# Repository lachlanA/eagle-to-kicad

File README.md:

### **Converting from Eagle to KiCad.**
*    [Quick Introduction Video (DEAD LINK, MOVING to NEW SERVER)](http://cosmosc.com/video/testtital.mp4)  
     *Recommended video player [Firefox 87.0+](https://www.mozilla.org/en-US/firefox/desktop/) with [VLC video player plugin](http://www.videolan.org/vlc/)*  

* The following 5 **ulp** (eagle *user script file*) and one **ulp** include file, work together or stand alone to convert **Eagle** *sch/pcb* version 6.xx*(7.xx-8.xx maybe?)* file(s) and any version of Eagle lib(*lbr*) to **KiCad** *sch/pcb* and *lib/mod* files.  

* The Programs will do
    * Eagle multi sheet schematic to KiCad multi sheets.  
	* Global and local net labels for multi sheets. *(This is a real nasty bit of hacking!)*
	* Multi part gates.  
	* Build KiCad PCB modules and sch libs from Eagle sch.  
	* Make project director to store all the converted files.  
	* And basic error checking.  
	* Eagle 6.xx(7.xx-8.xx?) PCB files can be directly import to KiCad.  
	* Eagle *LBR*s (any version of Eagle libs or size ) can be converted to KiCad lib/mod using eagle-lbr2kicad-1.0.ulp see [Eagle Lib conversion]( https://github.com/lachlanA/eagle-to-kicad-libs) for more details.  
	* Converts VIA to Pads, which helps with KiCad's flood fill, when VIAs have no connections.  
	* Documents fills over SMD pads on Eagle Layer 155,156  
	* Documents on layer's 150,152,153,154 of (Eagle) the unconnected VIAs and tracks.  
	* The **[examples](https://github.com/lachlanA/eagle-to-kicad/tree/master/examples)** directory contains a number of converted schematics/boards.  

* By using the following **ulp**s  a consistent link from the schematic to PCB is maintained so forward and backward net-list annotations work under KiCad!  

* **WARNINGS, AND NASTY SURPRISES, PLEASE READ!!!**
* **Only works correctly for version 4.7, or 5.1.(X?) of KiCad, it may not on other version.**
* **In KiCad Eagle PCB import of vias and tracks don't retain their NET information if they are not connected to a pad with a track, whereas they do in Eagle, (KiCad assigns a null net-name on Eagle PCB import in KiCad's Pcbnew).***  
***The result will be KiCad flood fill will not connect to them!!! There is an option to convert and document on layers 150,152,153,154 of (Eagle) the unconnected VIAs and tracks which will make finding and fixing the problem much easier.***
* ***Schematics wire's/nets can terminate in a bus or onto another wire/net/pad and not be connected in Eagle!!
Whereas in KiCad schematic wires to wires and wires to pads which terminates at the same location will be connected!!***  
* ***Eagle oval pad shapes are not supported in KiCad, you will only end up with a round pad!!***  
* ***Eagle PCB design rules are not imported by KiCads Pcbnew.***  

### Installing.
* Download the zip file, and unzip using your favorite zip program to your target directory *OR* if your prefer git:

			git clone https://github.com/lachlanA/eagle-to-kicad.git  

* **WARNING:**  The ULPs file-name will conflict with Eagles ULPs file-names so  
  **DO NOT install them in Eagle's ULP directory**  

* There are 5 **ULPs** and one **ULP** include file have been hack together.  
***run-me-first-from-eagle-sch.ulp*** .....   stage 1: Start here,  script missing number(s) to parts prefixes.  
***fix_via_hack.ulp*** ..............................   stage 2: Converts unconnected VIAs to pads.  
***eagle6xx-sch-to-kicad-sch.ulp*** ....    stage 3: Build sch and project files, etc  
***exp-lbrs.ulp*** .......................................   stage 4: Extract libs from eagle schematic/PCB  
***eagle-lbr2kicad-1.0.ulp***....................  stage 5: Converts Eagle lbr to KiCad lib/mod  
***eagle_to_kicad_include.inc*** ..........  Include file used by the other 4 ULP\s  

### HOW TO RUN THE ULPs 
 
 **WARNING Always backup your Eagle sch/PCB files before running this program!**  
 
1. Start your Eagle program *(Make sure your using  version 6.xx of Eagle)*

2. Open the eagle sch/PCB  file you wish to convert. Make sure the eagle sch and PCB files are both, Correct and pass all ERC/DRC checks in Eagle.  

3. Next Open the top left hand  **File menu** and select  **Run ULP**  

4. A file requester window will open. Use this to find the location of the ***run-me-first-from-eagle-sch.ulp*** ULP you download from this website. We use this script to make sure all part prefixes are ending in a number  IE:   R0,  X1   etc. as KiCad will ask to renumber any prefix which does not end in a number. *(It may do this any way, but don't worry it won't change any prefixes which have already been numbered unless you tell it too!)*  Keeping prefixes consistent from schematic to PCB will allow net-list forward and back annotation to work in KiCad. Select **OK** *(this will run the script)*.  When this completes all references without a number should have a number appended to them. Note: This number will start from the largest reference number on the sch/PCB.

5. Next stage will run automatically, ***fix_via_hack.ulp*** This will check for free unconnected VIAs and convert them to pads,  this is very much a hack, as it changes the Eagle sch/PCB files.  The changed files are saved in ***targetdir/modified_eagle_files/*** There are 2 option's Document the VIAs/pads buy putting a ***>*** and net lable name on the VIA/pad on **layer 51** for Eagle, and **Dwgs.User** for KiCad. Second option is to Not to convert the VIAs to pads.  
The ulp hack adds pad's to the sch file, at **X,Y 0,0** this may conflict with any net/part at this location, so please move the sch/PCB contents so there are no parts/nets at this location before running the script.
You may getting warnings from Eagle about connecting net??? to a power plan net, just click OK, as this is normal for this script.

6. Next stage will run automatically. Set the option/location of the download ULP. And also Make sure you make/select a ***clean target directory*** where all the KiCad files will be put. Select OK, And with luck you should have sch part done. The previous ULP will link automatically to ***exp-lbrs.ulp*** for the  next step: If you have selected extract the KiCad lib's from Eagle sch/PCB *(The default).* This ULP will build Eagle lbr file, *Note: this can be a very slow process,  and will leave the Eagle PCB editor window open when complete*. Just ignore this for the moment. If this complete OK, the previous ULP will link to ***eagle-lbr2kicad-1.0.ulp*** which will convert the Eagle lbr file to a KiCad lib/mod files.  The ***eagle-lbr2kicad-1.0.ulp*** window will open with quite a few options. Just select OK for the moment.  And if *Murphy's Law is sound asleep* we should have the target directory with all the converted files, including KiCad project files. But with one exception, it will be missing KiCad PCB file.

7. For this, we need to Open KiCad's **pcbnew** program directly, at the command prompt ("c:\Program Files\KiCad\bin\pcbnew.exe"). *If you make the mistake of not opening **pcbnew** directly, and instead chose to run it from KiCad's **pcbnew**  menu. You will have no option for importing the Eagle 6 PCB file!*  In Pcbnew click on **File->Import Non-KiCad Board File...**, a window will pop-up. Select the PCB eagle file linked to the eagle sch file we used at the beginning. On the lower right side you will have a drop down menu box option, select **Eagle ver. 6.x XML PCB files (\*.b**, and press OK. After importing the Eagle PCB file, (without errors I hope). Do a **SAVE AS** to **PROJECTNAME.kicad_pcb** to the new target directory *(where you saved the output from to preceding ULP's to).* **PROJECTNAME** being the name you give to your project early on. As a helper a dummy kicad_pcb file with the correct name has been created in the target directory which you can use to do a Save-As to.

8. Next step is to check the KiCad **sch** and KiCad **PCB** are consistent for parts and nets. Start **KiCad**, and open the project in the newly created target directory. Open the sch file. And if it was converted from the single sch file, you should have the **sch** file in the display. Or multi sheet **sch** file you will have a number of small boxes spread across the page. Each one of those boxes being a converted Eagle sub-sheet. Click on the first one and check for errors. All being good, click on Generate Net-list, and click OK. It may ask to Annotate the **schematic**. If so do the Annotation step. And then come back and click on Generate net-list. And Generate it.

9. Next click on **CvPcb**, this assigns the PCB footprints with the sch parts. Most likely you will get the following warning: *Some of the assigned footprints are legacy entries (are missing lib nicknames). Would you like CvPcb to attempt to convert them to the new required FPID format? (If you answer no, then these assignments will be cleared out and you will have to re-assign these footprints yourself.)* Just click the yes button. And a window will open up listing all the parts and footprints which it has assigned. Under FILE menu click Save. And then File Close.

10. Next Clink on **PcbNew** button on the top menu, and the PCB should open up. Now click on the **NetList** and a window should open up, from there click on Read Current Net-list. All going well you should not have any extra parts added, and only a few warning's about changing net list names.  And you should be done. Please check over the converted **sch/PCB** as there are many things which can go wrong! While I have tried to catch as many conversion problem, I expect there many still waiting to be found. ***So check and triple check the results!!!***

**NOTES:**   For more info on KiCad https://www.kicad.org/display/KICAD/Installing+KiCad  
As KiCad is the process of major upgrade, and enhancement. Please be nice when asking questions of the Development team. I think you will love the new Push and shove router. This feature alone makes it worth while moving from Eagle to KiCad. I hope these ULPs make the job a lot easier.

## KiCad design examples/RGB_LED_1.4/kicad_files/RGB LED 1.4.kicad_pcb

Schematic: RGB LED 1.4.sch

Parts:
C1, C2, C3: 0.1uF; CAP-PTH-SMALL
IC1, IC2, IC3: TLC9450NT; DIL28-3
JP2: ARDUINO POWER; 1X06_LOCK
JP3: ARDUINO ANALOG; 1X06_LOCK
JP4: ARDUINO D13-8; 1X08_LOCK
JP5: ARDUINO D7-0; 1X08_LOCK
JP11: 1X02_LOCK
JP12, JP13: 1X05_LOCK
JP20, JP21: 1X04_LOCK
LED11, LED12, LED13, LED14, LED21, LED22, LED23, LED24, LED31, LED32, LED33, LED34, LED41, LED42, LED43, LED44: LED-TRICOLOR-THROUGHHOLE
R1, R2, R3: 2K; 0309_12
R4: 10K; 0309_12
SW1, SW2, SW3: TACTILE-PTH
SWRESET45: RESET; TACTILE-PTH

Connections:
B11: IC3.28 (OUT0), LED11.GRN
B12: IC3.1 (OUT1), LED12.GRN
B13: IC3.2 (OUT2), LED13.GRN
B14: IC3.3 (OUT3), LED14.GRN
B21: IC3.4 (OUT4), LED21.GRN
B22: IC3.5 (OUT5), LED22.GRN
B23: IC3.6 (OUT6), LED23.GRN
B24: IC3.7 (OUT7), LED24.GRN
B31: IC3.8 (OUT8), LED31.GRN
B32: IC3.9 (OUT9), LED32.GRN
B33: IC3.10 (OUT10), LED33.GRN
B34: IC3.11 (OUT11), LED34.GRN
B41: IC3.12 (OUT12), LED41.GRN
B42: IC3.13 (OUT13), LED42.GRN
B43: IC3.14 (OUT14), LED43.GRN
B44: IC3.15 (OUT15), LED44.GRN
BLANK: IC1.23 (BLANK), IC2.23 (BLANK), IC3.23 (BLANK), JP4.3, JP21.3, R4.1
G11: IC2.28 (OUT0), LED11.BLU
G12: IC2.1 (OUT1), LED12.BLU
G13: IC2.2 (OUT2), LED13.BLU
G14: IC2.3 (OUT3), LED14.BLU
G21: IC2.4 (OUT4), LED21.BLU
G22: IC2.5 (OUT5), LED22.BLU
G23: IC2.6 (OUT6), LED23.BLU
G24: IC2.7 (OUT7), LED24.BLU
G31: IC2.8 (OUT8), LED31.BLU
G32: IC2.9 (OUT9), LED32.BLU
G33: IC2.10 (OUT10), LED33.BLU
G34: IC2.11 (OUT11), LED34.BLU
G41: IC2.12 (OUT12), LED41.BLU
G42: IC2.13 (OUT13), LED42.BLU
G43: IC2.14 (OUT14), LED43.BLU
G44: IC2.15 (OUT15), LED44.BLU
GND: C1.2, C2.2, C3.2, IC1.22 (GND), IC1.27 (VPRG), IC2.22 (GND), IC2.27 (VPRG), IC3.22 (GND), IC3.27 (VPRG), JP2.3, JP20.2, R1.1, R2.1, R3.1, SW1.3, SW1.4, SW2.3, SW2.4, SW3.3, SW3.4, SWRESET45.3, SWRESET45.4
GSCLK: IC1.18 (GSCLK), IC2.18 (GSCLK), IC3.18 (GSCLK), JP5.4, JP21.4
unnamed: IC1.17 (SOUT), IC2.26 (SIN)
unnamed: IC2.17 (SOUT), IC3.26 (SIN)
unnamed: JP12.3, SW1.1, SW1.2
unnamed: IC3.20 (IREF), R3.2
unnamed: IC2.20 (IREF), R2.2
unnamed: IC1.20 (IREF), R1.2
unnamed: JP12.4, SW2.1, SW2.2
unnamed: JP12.5, SW3.1, SW3.2
R11: IC1.28 (OUT0), LED11.RED
R12: IC1.1 (OUT1), LED12.RED
R13: IC1.2 (OUT2), LED13.RED
R14: IC1.3 (OUT3), LED14.RED
R21: IC1.4 (OUT4), LED21.RED
R22: IC1.5 (OUT5), LED22.RED
R23: IC1.6 (OUT6), LED23.RED
R24: IC1.7 (OUT7), LED24.RED
R31: IC1.8 (OUT8), LED31.RED
R32: IC1.9 (OUT9), LED32.RED
R33: IC1.10 (OUT10), LED33.RED
R34: IC1.11 (OUT11), LED34.RED
R41: IC1.12 (OUT12), LED41.RED
R42: IC1.13 (OUT13), LED42.RED
R43: IC1.14 (OUT14), LED43.RED
R44: IC1.15 (OUT15), LED44.RED
RESET: JP2.6, SWRESET45.1, SWRESET45.2
SCLK: IC1.25 (SCLK), IC2.25 (SCLK), IC3.25 (SCLK), JP12.2, JP21.1
SCLK_DEF: JP4.6, JP13.2
SIN: IC1.26 (SIN), JP12.1
SIN_DEF: JP4.4, JP13.1
SOUT: IC3.17 (SOUT), JP20.3
SW1_DEF: JP5.3, JP13.3
SW2_DEF: JP5.5, JP13.4
SW3_DEF: JP5.8, JP13.5
VCC: C1.1, C2.1, C3.1, IC1.19 (DCPRG), IC1.21 (VCC), IC2.19 (DCPRG), IC2.21 (VCC), IC3.19 (DCPRG), IC3.21 (VCC), JP2.4, JP11.1, JP20.4, R4.2
VLED: JP11.2, JP20.1, LED11.GND (A), LED12.GND (A), LED13.GND (A), LED14.GND (A), LED21.GND (A), LED22.GND (A), LED23.GND (A), LED24.GND (A), LED31.GND (A), LED32.GND (A), LED33.GND (A), LED34.GND (A), LED41.GND (A), LED42.GND (A), LED43.GND (A), LED44.GND (A)
XLAT: IC1.24 (XLAT), IC2.24 (XLAT), IC3.24 (XLAT), JP4.2, JP21.2

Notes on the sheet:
HTINK RGB Shield 1.3
(C) 2009, Ben Combee
Creative Commons Attribution-Share Alike 3.0 License
http://combee.net/rgbshield
Allows connecting other voltage to LEDs

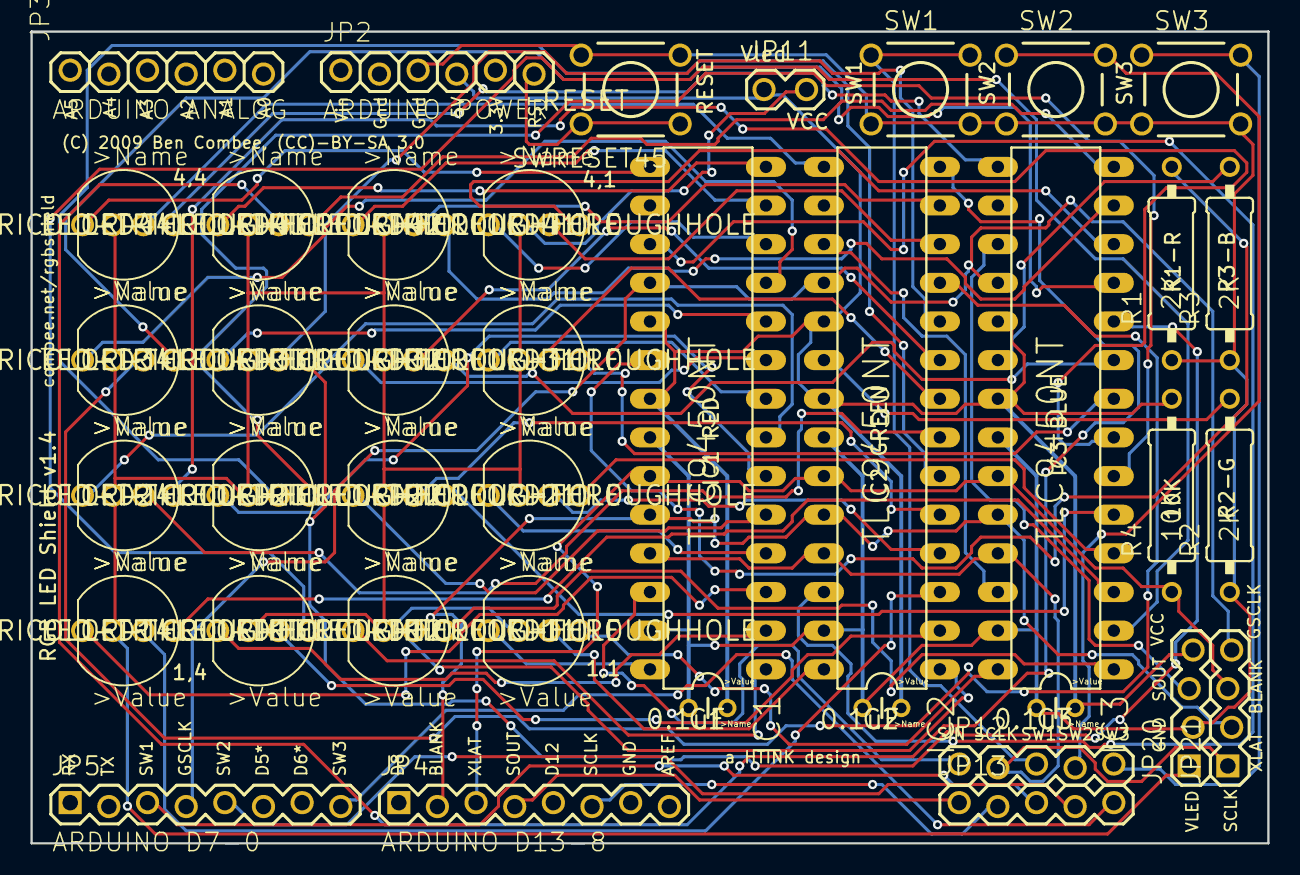
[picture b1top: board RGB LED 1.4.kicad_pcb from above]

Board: 2 copper layers, 81.3 x 53.3 mm, 39 parts (0 on the bottom side), 71 nets.

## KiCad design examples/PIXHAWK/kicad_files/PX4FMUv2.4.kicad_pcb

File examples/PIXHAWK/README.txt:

NOTE: ***** USE AT YOUR OWN RISK *****

This contains the eagle file's from PX4 Autopilot Project from git-hub, at https://github.com/PX4 which have been
convert to KiCad. Via's have been converted to Pad, and the modified Eagle files are in

  kicad_files/modified_eagle_files/

The original Eagle files are in

  eagle_original_files/

Also note the Eagle files have been converted to version 6.xx of eagle.
Note:  No Adjustment of power plan's had been made, you will need to adjust them to get correct connection's
       and spacing etc. And as away triple check you results.

sources at:   https://github.com/PX4

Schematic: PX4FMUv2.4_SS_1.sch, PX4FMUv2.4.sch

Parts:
C101: 0u1; PIXHAWK2_0402-CAP
C102, C103: 8p; PIXHAWK2_0402-CAP
R101: 470R; PIXHAWK2_0402-RES
R102: 10K; PIXHAWK2_0402-RES
U101: STM32F4X7VX; PIXHAWK2_TQFP100
U102: FM25V01; PIXHAWK2_SO08
X101: 3.2x2.5 mm / 24 MHz / 15 ppm; PIXHAWK2_OSCILLATOR-3.2X2.5

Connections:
!ACCEL_MAG_CS: U101.9 (PC15); also elsewhere on the board
!BARO_CS: U101.88 (PD7); also elsewhere on the board
!FMU-LED_AMBER: U101.43 (PE12); also elsewhere on the board
!FRAM_CS: U101.57 (PD10), U102.1 (!S)
!GYRO_CS: U101.7 (PC13); also elsewhere on the board
!MPU_CS: U101.17 (PC2); also elsewhere on the board
!SPI_EXT_NSS: U101.3 (PE4); also elsewhere on the board
!VBUS_VALID: U101.15 (PC0); also elsewhere on the board
!VDD_5V_HIPOWER_OC: U101.41 (PE10); also elsewhere on the board
!VDD_5V_PERIPH_EN: U101.67 (PA8); also elsewhere on the board
!VDD_5V_PERIPH_OC: U101.46 (PE15); also elsewhere on the board
!VDD_BRICK_VALID: U101.91 (PB5); also elsewhere on the board
!VDD_SERVO_VALID: U101.93 (PB7); also elsewhere on the board
ACCEL_DRDY: U101.90 (PB4); also elsewhere on the board
ALARM: U101.77 (PA15); also elsewhere on the board
BATT_CURRENT_SENS: U101.26 (PA3); also elsewhere on the board
BATT_VOLTAGE_SENS: U101.25 (PA2); also elsewhere on the board
CAN1_RX: U101.81 (PD0); also elsewhere on the board
CAN1_TX: U101.82 (PD1); also elsewhere on the board
CAN2_RX: U101.51 (PB12); also elsewhere on the board
CAN2_TX: U101.92 (PB6); also elsewhere on the board
FMU-CH1: U101.45 (PE14); also elsewhere on the board
FMU-CH2: U101.44 (PE13); also elsewhere on the board
FMU-CH3: U101.42 (PE11); also elsewhere on the board
FMU-CH4: U101.40 (PE9); also elsewhere on the board
FMU-CH5: U101.60 (PD13); also elsewhere on the board
FMU-CH6: U101.61 (PD14); also elsewhere on the board
FMU-I2C1_SCL: U101.95 (PB8); also elsewhere on the board
FMU-I2C1_SDA: U101.96 (PB9); also elsewhere on the board
FMU-I2C2_SCL: U101.47 (PB10); also elsewhere on the board
FMU-I2C2_SDA: U101.48 (PB11); also elsewhere on the board
FMU-SWCLK: U101.76 (PA14); also elsewhere on the board
FMU-SWDIO: U101.72 (PA13); also elsewhere on the board
FMU-SWO: U101.89 (PB3); also elsewhere on the board
FMU-UART4_RX: U101.24 (PA1); also elsewhere on the board
FMU-UART4_TX: U101.23 (PA0); also elsewhere on the board
FMU-UART7_RX: U101.38 (PE7); also elsewhere on the board
FMU-UART7_TX: U101.39 (PE8); also elsewhere on the board
FMU-UART8_RX: U101.97 (PE0); also elsewhere on the board
FMU-UART8_TX: U101.98 (PE1); also elsewhere on the board
FMU-USART2_CTS: U101.84 (PD3); also elsewhere on the board
FMU-USART2_RTS: U101.85 (PD4); also elsewhere on the board
FMU-USART2_RX: U101.87 (PD6); also elsewhere on the board
FMU-USART2_TX: U101.86 (PD5); also elsewhere on the board
FMU-USART3_CTS: U101.58 (PD11); also elsewhere on the board
FMU-USART3_RTS: U101.59 (PD12); also elsewhere on the board
FMU-USART3_RX: U101.56 (PD9); also elsewhere on the board
FMU-USART3_TX: U101.55 (PD8); also elsewhere on the board
FMU-VDD_3V3: C101.P$1 (1), U102.3 (!W), U102.7 (!HOLD), U102.8 (VDD); also elsewhere on the board
FMU_AUX_ADC1: U101.18 (PC3); also elsewhere on the board
FMU_AUX_ADC2: U101.33 (PC4); also elsewhere on the board
FRAM_MISO: U101.53 (PB14), U102.2 (Q)
FRAM_MOSI: U101.54 (PB15), U102.5 (D)
FRAM_SCK: U101.52 (PB13), U102.6 (C)
GND: C101.P$2 (2), C102.P$2 (2), C103.P$1 (1), R102.P$2 (2), U102.4 (VSS), X101.2 (NC_2), X101.4 (NC_4); also elsewhere on the board
GPIO_EXT_1: U101.8 (PC14); also elsewhere on the board
GYRO_DRDY: U101.35 (PB0); also elsewhere on the board
IO-USART1_TX: R101.P$2 (2); also elsewhere on the board
MAG_DRDY: U101.36 (PB1); also elsewhere on the board
MPU_DRDY: U101.62 (PD15); also elsewhere on the board
unnamed: C103.P$2 (2), U101.13 (OSC_OUT), X101.1
unnamed: C102.P$1 (1), U101.12 (OSC_IN), X101.3
unnamed: R101.P$1 (1), U101.69 (PA10)
OTG_FS_DM: U101.70 (PA11); also elsewhere on the board
OTG_FS_DP: U101.71 (PA12); also elsewhere on the board
PB2-BOOT1: R102.P$1 (1), U101.37 (PB2)
PRESSURE_SENS: U101.34 (PC5); also elsewhere on the board
SDIO_CK: U101.80 (PC12); also elsewhere on the board
SDIO_CMD: U101.83 (PD2); also elsewhere on the board
SDIO_D0: U101.65 (PC8); also elsewhere on the board
SDIO_D1: U101.66 (PC9); also elsewhere on the board
SDIO_D2: U101.78 (PC10); also elsewhere on the board
SDIO_D3: U101.79 (PC11); also elsewhere on the board
SERIAL_FMU_TO_IO: U101.63 (PC6); also elsewhere on the board
SERIAL_IO_TO_FMU: U101.64 (PC7); also elsewhere on the board
SPI_EXT_MISO: U101.4 (PE5); also elsewhere on the board
SPI_EXT_MOSI: U101.5 (PE6); also elsewhere on the board
SPI_EXT_SCK: U101.1 (PE2); also elsewhere on the board
SPI_INT_MISO: U101.31 (PA6); also elsewhere on the board
SPI_INT_MOSI: U101.32 (PA7); also elsewhere on the board
SPI_INT_SCK: U101.30 (PA5); also elsewhere on the board
VBUS: U101.68 (PA9); also elsewhere on the board
VDD_3V3_SENSORS_EN: U101.2 (PE3); also elsewhere on the board
VDD_5V_SENS: U101.29 (PA4); also elsewhere on the board

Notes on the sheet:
FMU SoC Ports FRAM
Note: MAG/ACCEL/GYRO_DRDY pins chosen for both timer capture and separate EXTI operaton. EXTI0 - TIM3_CH3 - GYRO1 EXTI1 - <free> EXTI2 - <free> EXTI3 - <free> EXTI4 - TIM3_CH1 - ACCEL EXTI5-9 - TIM3_CH2 - MAG
Timer allocation: PE9: TIM1_CH1: FMU-CH4 PE11: TIM1_CH2: FMU-CH3 PE13: TIM1_CH3: FMU-CH2 PE14: TIM1_CH4: FMU-CH1 PA15: TIM2_CH1: ALARM PB0: TIM3_CH3: GYRO1_DRDY PB1: TIM3_CH4: GYRO2_DRDY PB4: TIM3_CH1: ACCEL_DRDY PB5: TIM3_CH2: MAG_DRDY PD13: TIM4_CH2: FMU-CH5 PD14: TIM4_CH3: FMU-CH6 PD15: TIM4_CH4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
IO debug console
Spare ADC
ALL SHEETS SAME REVISION

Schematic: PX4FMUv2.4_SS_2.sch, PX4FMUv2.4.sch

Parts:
C201, C202: 0u1; PIXHAWK2_0402-CAP
D201, D202, D203: PESD0402-140; PIXHAWK2_0402-TVS
J201, J202, J203, J204: DF13C-6P-1.25V; CON-HIROSE-DF13_DF13C-6P-1.25V
L201, L202, L203: KNH16C104DA5TS; PIXHAWK2_KYOCERA-KNH16-DA
R201, R202, R203, R204, R205, R206, R207, R208, R209, R210, R211, R212, R213, R214, R215, R216: 120R; PIXHAWK2_0402-RES
U201, U202: TXS0108QFN20; PIXHAWK2_QFN20-RGY

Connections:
CAN2_RX: R216.P$1 (1); also elsewhere on the board
CAN2_TX: R215.P$1 (1); also elsewhere on the board
FMU-UART4_RX: U202.8 (A7); also elsewhere on the board
FMU-UART4_TX: U202.9 (A8); also elsewhere on the board
FMU-UART7_RX: U202.4 (A3); also elsewhere on the board
FMU-UART7_TX: U202.5 (A4); also elsewhere on the board
FMU-UART8_RX: U202.6 (A5); also elsewhere on the board
FMU-UART8_TX: U202.7 (A6); also elsewhere on the board
FMU-USART2_CTS: U201.9 (A8); also elsewhere on the board
FMU-USART2_RTS: U201.8 (A7); also elsewhere on the board
FMU-USART2_RX: U201.6 (A5); also elsewhere on the board
FMU-USART2_TX: U201.7 (A6); also elsewhere on the board
FMU-USART3_CTS: U201.3 (A2); also elsewhere on the board
FMU-USART3_RTS: U201.1 (A1); also elsewhere on the board
FMU-USART3_RX: U201.4 (A3); also elsewhere on the board
FMU-USART3_TX: U201.5 (A4); also elsewhere on the board
FMU-VDD_3V3: C201.P$1 (1), C202.P$1 (1), U201.2 (VCCA), U201.10 (OE), U201.19 (VCCB), U202.2 (VCCA), U202.10 (OE), U202.19 (VCCB); also elsewhere on the board
GND: C201.P$2 (2), C202.P$2 (2), D201.A, D202.A, D203.A, J201.6, J202.6, J203.6, J204.6, L201.P$3, L201.P$4, L201.P$5, L202.P$3, L202.P$4, L202.P$5, L203.P$3, L203.P$4, L203.P$5, U201.11 (GND), U202.11 (GND); also elsewhere on the board
unnamed: D201.C, J201.1, L201.P$2
unnamed: J203.4, R215.P$2 (2)
unnamed: J203.5, R216.P$2 (2)
unnamed: R201.P$1 (1), U201.20 (B1)
unnamed: R208.P$1 (1), U201.18 (B2)
unnamed: R202.P$1 (1), U201.17 (B3)
unnamed: R209.P$1 (1), U201.16 (B4)
unnamed: R203.P$1 (1), U201.15 (B5)
unnamed: R210.P$1 (1), U201.14 (B6)
unnamed: R204.P$1 (1), U201.13 (B7)
unnamed: R211.P$1 (1), U201.12 (B8)
unnamed: R207.P$1 (1), U202.13 (B7)
unnamed: R214.P$1 (1), U202.12 (B8)
unnamed: R205.P$1 (1), U202.17 (B3)
unnamed: R212.P$1 (1), U202.16 (B4)
unnamed: R206.P$1 (1), U202.15 (B5)
unnamed: R213.P$1 (1), U202.14 (B6)
unnamed: D203.C, J203.1, J204.1, L203.P$2
unnamed: D202.C, J202.1, L202.P$2
SERIAL1_CTS: J201.4, R211.P$2 (2)
SERIAL1_RTS: J201.5, R204.P$2 (2)
SERIAL1_RX: J201.3, R203.P$2 (2); also elsewhere on the board
SERIAL1_TX: J201.2, R210.P$2 (2); also elsewhere on the board
SERIAL2_CTS: J202.4, R208.P$2 (2)
SERIAL2_RTS: J202.5, R201.P$2 (2)
SERIAL2_RX: J202.3, R202.P$2 (2); also elsewhere on the board
SERIAL2_TX: J202.2, R209.P$2 (2); also elsewhere on the board
SERIAL3_RX: J203.3, R207.P$2 (2); also elsewhere on the board
SERIAL3_TX: J203.2, R214.P$2 (2); also elsewhere on the board
SERIAL4_RX: J204.3, R206.P$2 (2); also elsewhere on the board
SERIAL4_TX: J204.2, R213.P$2 (2); also elsewhere on the board
SERIAL5_RX: J204.5, R205.P$2 (2); also elsewhere on the board
SERIAL5_TX: J204.4, R212.P$2 (2); also elsewhere on the board
VDD_5V_HIPOWER: L201.P$1; also elsewhere on the board
VDD_5V_PERIPH: L202.P$1, L203.P$1; also elsewhere on the board

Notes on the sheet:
FMU Serial ports
SERIAL2
SERIAL1
SERIAL3
SERIAL4
Default GPS port

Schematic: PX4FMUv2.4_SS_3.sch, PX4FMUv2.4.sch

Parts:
J301: 47346-0001; PIXHAWK2_MOLEX-47346-0001
J302: DF13C-4P-1.25V; CON-HIROSE-DF13_DF13C-4P-1.25V
JX301: ARM_MINI_JTAG-SMT; PIXHAWK2_FTSH-105-01-XXX-DV-K
R301, R302, R303, R304, R305: 100K; PIXHAWK2_0402-RES
R306, R307: 1K5; PIXHAWK2_0402-RES
U301: 2908-05WB-MG; BASEBOARD_MICROSD
U302: NUF2042XV6; PIXHAWK2_SOT563-6

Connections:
FMU-I2C2_SCL: R306.P$1 (1); also elsewhere on the board
FMU-I2C2_SDA: R307.P$1 (1); also elsewhere on the board
FMU-SWCLK: JX301.4; also elsewhere on the board
FMU-SWDIO: JX301.2; also elsewhere on the board
FMU-SWO: JX301.6; also elsewhere on the board
FMU-VDD_3V3: JX301.1, R301.P$2 (2), R302.P$2 (2), R303.P$2 (2), R304.P$2 (2), R305.P$2 (2), R306.P$2 (2), R307.P$2 (2), U301.4 (VCC); also elsewhere on the board
GND: J301.GND (5), J301.GND1, J301.GND2, J301.GND3, J301.GND4, J302.4, JX301.3, JX301.5, JX301.9, U301.6 (GND), U302.2 (GND); also elsewhere on the board
OTG_DM1: J301.D- (2), J302.3, U302.1 (D1I)
OTG_DP1: J301.D+ (3), J302.2, U302.3 (D2I)
OTG_FS_DM: U302.6 (D1O); also elsewhere on the board
OTG_FS_DP: U302.4 (D2O); also elsewhere on the board
SDIO_CK: U301.5 (CLK); also elsewhere on the board
SDIO_CMD: R303.P$1 (1), U301.3 (CMD); also elsewhere on the board
SDIO_D0: R304.P$1 (1), U301.7 (D0); also elsewhere on the board
SDIO_D1: R305.P$1 (1), U301.8 (D1); also elsewhere on the board
SDIO_D2: R301.P$1 (1), U301.1 (D2); also elsewhere on the board
SDIO_D3: R302.P$1 (1), U301.2 (D3); also elsewhere on the board
VBUS: J301.VBUS (1), J302.1, U302.5 (VBUS); also elsewhere on the board

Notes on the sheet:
USB microSD Expansion
microSD
To be used with panel- mount micro USB connectors: - Amphenol MUSBK15230

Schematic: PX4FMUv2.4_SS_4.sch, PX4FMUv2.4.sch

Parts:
C401, C402: 0u1; PIXHAWK2_0402-CAP
D401, D402, D403, D404: PESD0402-140; PIXHAWK2_0402-TVS
J401, J405: DF13C-4P-1.25V; CON-HIROSE-DF13_DF13C-4P-1.25V
J402: DF13C-3P-1.25V; CON-HIROSE-DF13_DF13C-3P-1.25V
J403: DF13C-7P-1.25V; CON-HIROSE-DF13_DF13C-7P-1.25V
J404: DF13C-5P-1.25V; CON-HIROSE-DF13_DF13C-5P-1.25V
L401, L402, L403, L404: KNH16C104DA5TS; PIXHAWK2_KYOCERA-KNH16-DA
R401, R402: 1K5; PIXHAWK2_0402-RES
R403, R406, R407, R408: 10K/0.1%; PIXHAWK2_0402-RES
R404, R405, R409: 120R; PIXHAWK2_0402-RES
U401: MAX3051; PIXHAWK2_SOT23-8

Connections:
!SPI_EXT_NSS: J403.5; also elsewhere on the board
CAN1_RX: U401.4 (DOUT); also elsewhere on the board
CAN1_TX: U401.1 (DIN); also elsewhere on the board
CAN_H: J405.2, R409.P$1 (1), U401.7 (CANH); also elsewhere on the board
CAN_L: J405.3, R409.P$2 (2), U401.6 (CANL); also elsewhere on the board
FMU-I2C1_SCL: R401.P$1 (1), R404.P$1 (1); also elsewhere on the board
FMU-I2C1_SDA: R402.P$1 (1), R405.P$1 (1); also elsewhere on the board
FMU-VDD_3V3: C402.P$1 (1), R401.P$2 (2), R402.P$2 (2), U401.3 (VCC); also elsewhere on the board
FMU_AUX_ADC1: R408.P$1 (1); also elsewhere on the board
FMU_AUX_ADC1_PROT: J404.4, R408.P$2 (2)
FMU_AUX_ADC2: R407.P$1 (1); also elsewhere on the board
FMU_AUX_ADC2_PROT: J404.2, R407.P$2 (2)
GND: C401.P$2 (2), C402.P$2 (2), D401.A, D402.A, D403.A, D404.A, J401.4, J402.3, J403.7, J404.3, J404.5, J405.4, L401.P$3, L401.P$4, L401.P$5, L402.P$3, L402.P$4, L402.P$5, L403.P$3, L403.P$4, L403.P$5, L404.P$3, L404.P$4, L404.P$5, R403.P$1 (1), U401.2 (GND), U401.5 (SHDN), U401.8 (RS); also elsewhere on the board
GPIO_EXT_1: J403.6; also elsewhere on the board
unnamed: J401.2, R404.P$2 (2)
unnamed: J401.3, R405.P$2 (2)
unnamed: D402.C, J403.1, L402.P$2
unnamed: D401.C, J401.1, J402.1, L401.P$2
unnamed: D404.C, J405.1, L403.P$2
unnamed: D403.C, J404.1, L404.P$2
PRESSURE_SENS: C401.P$1 (1), R403.P$2 (2), R406.P$1 (1); also elsewhere on the board
PRESSURE_SENS_IN: J402.2, R406.P$2 (2); also elsewhere on the board
SPI_EXT_MISO: J403.3; also elsewhere on the board
SPI_EXT_MOSI: J403.4; also elsewhere on the board
SPI_EXT_SCK: J403.2; also elsewhere on the board
VDD_5V_PERIPH: L401.P$1, L402.P$1, L403.P$1, L404.P$1; also elsewhere on the board

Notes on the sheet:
SPI
PRESSURE
I2C1
AUX ADC PORTS
SPI I2C Analog pressure CAN Aux ADC ports
Note: SPI port is UNBUFFERED; only suitable for short connections.
Divider to scale from 5V to 3.3V (ratio of 0.5 chosen)

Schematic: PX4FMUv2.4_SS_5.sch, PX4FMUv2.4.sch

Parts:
C501, C506, C509, C511: 10u/10V; PIXHAWK2_0805-CAP
C502, C503, C507, C508, C514: 0u1; PIXHAWK2_0402-CAP
C504, C505: 10n; PIXHAWK2_0402-CAP
C510: 0u47; PIXHAWK2_0402-CAP
C512, C513: 2u2; PIXHAWK2_0603-CAP
C515: 0u01; PIXHAWK2_0603-CAP
U501: L3GD20; PIXHAWK2_L3G4200DH-MAN
U502: L3GD20H; PIXHAWK2_LGA-16L
U504: LSM303D; PIXHAWK2_LGA-16L
U505: MPU-6000; PIXHAWK2_QFN-24
U506: MS5611-01BA; PIXHAWK2_MS5611-01BA
X503: 0512811094; PIXHAWK2_51281-1094

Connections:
!ACCEL_MAG_CS: U504.8 (CS), X503.6; also elsewhere on the board
!BARO_CS: U506.5 (CSB2); also elsewhere on the board
!GYRO_CS: U501.5 (CS), U502.5 (CS), X503.7; also elsewhere on the board
!MPU_CS: U505.8 (/CS); also elsewhere on the board
ACCEL_DRDY: U504.11 (INT1), X503.3; also elsewhere on the board
GND: C501.P$2 (2), C502.P$2 (2), C503.P$2 (2), C504.P$2 (2), C505.P$2 (2), C506.P$2 (2), C507.P$2 (2), C508.P$2 (2), C509.P$2 (2), C511.P$2 (2), C512.P$2 (2), C513.P$2 (2), C514.P$2 (2), C515.P$2 (2), U501.8 (RES_P8_GND), U501.9 (RES_P9_GND), U501.10 (RES_P10_GND), U501.11 (RES_P11_GND), U501.12 (RES_P12_GND), U501.13 (GND), U502.9 (GND), U502.10 (GND), U502.11 (GND), U502.12 (GND), U502.13 (GND), U504.5 (GND), U504.10 (RSRV), U504.12 (GND), U504.13 (GND), U504.16 (GND), U505.1 (CLKIN), U505.18 (GND), U506.2 (PS), U506.3 (GND), X503.2; also elsewhere on the board
GYRO_DRDY: U501.6 (DRDY/INT2), U502.6 (DRDY/INT2), X503.5; also elsewhere on the board
MAG_DRDY: U504.9 (INT2), X503.4; also elsewhere on the board
MPU_DRDY: U505.12 (INT); also elsewhere on the board
unnamed: C509.P$1 (1), U504.15 (C1)
unnamed: C510.P$1 (1), U504.2 (SETC)
unnamed: C510.P$2 (2), U504.3 (SETP)
unnamed: C505.P$1 (1), U502.14 (CAP)
unnamed: C504.P$1 (1), U501.14 (PLLFILT)
unnamed: C512.P$1 (1), U505.10 (REGOUT)
unnamed: C515.P$1 (1), U505.20 (CPOUT)
SPI_INT_MISO: U501.4 (SDO/SA0), U502.4 (SDO/SA0), U504.7 (SDO/SA0), U505.9 (AD0/SDO), U506.6 (SDO), X503.9; also elsewhere on the board
SPI_INT_MOSI: U501.3 (SDA/SDI/SDO), U502.3 (SDA/SDI/SDO), U504.6 (SDA/SDI/SDO), U505.24 (SDA/SDI), U506.7 (SDI/SDA), X503.8; also elsewhere on the board
SPI_INT_SCK: U501.2 (SCL/SPC), U502.2 (SCL/SPC), U504.4 (SCL/SPC), U505.23 (SCL/SCLK), U506.8 (SCLK), X503.10; also elsewhere on the board
VDD_3V3_SENSORS: C501.P$1 (1), C502.P$1 (1), C503.P$1 (1), C506.P$1 (1), C507.P$1 (1), C508.P$1 (1), C511.P$1 (1), C513.P$1 (1), C514.P$1 (1), U501.1 (VDD_IO), U501.15 (RES_P15_VDD), U501.16 (VDD), U502.1 (VDD_IO), U502.15 (VDD), U502.16 (VDD), U504.1 (VDD_IO), U504.14 (VDD), U505.13 (VDD), U506.1 (VDD), X503.1; also elsewhere on the board

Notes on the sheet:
Sensors
Switch to L3GD20H once available (Q3/2013) WARNING: DIFFERENT HW, SW COMPATIBLE
NOTE: place 10uF cap close to gyros
Stuff option 1: L3GD20 (legacy gyro)
Stuff option 2: L3GD20H (replacement gyro)
Stuff option 4: onboard accel/mag
Valid stuff option combos: 1 + 4 + 5 2 + 4 + 5 3 + 5 ONLY DO NOT stuff 1 + 2 at the same time DO NOT stuff 3 with any of 1, 2 or 4
Stuff option 5: MPU6000
Stuff option 3: offboard gyro/accel/mag
STUFF C503 WITH 220R RESISTOR

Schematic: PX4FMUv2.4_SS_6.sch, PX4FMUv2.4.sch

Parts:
B601: MS621FE; PIXHAWK2_MS621FE
C601: 10u/25V; PIXHAWK2_0805-CAP
C602: 10n; PIXHAWK2_0402-CAP
C603: 1u; PIXHAWK2_0603-CAP
C604, C605: 22u/25V; PIXHAWK2_0805-CAP
C606, C607, C608, C609, C610, C612, C615, C616, C617: 0u1; PIXHAWK2_0402-CAP
C611, C613: 2u2; PIXHAWK2_0603-CAP
C614, C618: 100u; PIXHAWK2_1206-CAP
D2: RB751V40T1G; PIXHAWK2_SOD323
L603: KNH16C104DA5TS; PIXHAWK2_KYOCERA-KNH16-DA
Q601: MMBT3906LT1SMD; TRANSISTOR-PNP_SOT23-BEC
R602, R604: 1M; PIXHAWK2_0402-RES
R603: 10k; PIXHAWK2_0402-RES
R608: 1K; PIXHAWK2_0402-RES
R609, R610: 10K/0.1%; PIXHAWK2_0402-RES
R611, R615: 10K; PIXHAWK2_0402-RES
R616: 25K5; PIXHAWK2_0402-RES
R617: 16K5; PIXHAWK2_0402-RES
R620: 1k8; PIXHAWK2_0402-RES
R621: 10R; PIXHAWK2_0603-RES
R635: DNP / 10k; PIXHAWK2_0402-RES
S601: RESET; PIXHAWK2_EVQP7J01K
U101: STM32F4X7VX; PIXHAWK2_TQFP100
U601, U602: BQ24315; PIXHAWK2_QFN8-DSG
U603: MIC5332; PIXHAWK2_MLF-8-EPAD

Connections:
!VDD_5V_HIPOWER_OC: R602.P$1 (1), U601.4 (!FAULT); also elsewhere on the board
!VDD_5V_PERIPH_EN: R615.P$1 (1), U601.5 (!CE), U602.5 (!CE); also elsewhere on the board
!VDD_5V_PERIPH_OC: R604.P$1 (1), U602.4 (!FAULT); also elsewhere on the board
FMU-!RESET: C609.P$2 (2), R635.P$1 (1), S601.A1 (1), U101.14 (NRST), U603.3 (POR2); also elsewhere on the board
FMU-BOOT0: R611.P$2 (2), U101.94 (BOOT0); also elsewhere on the board
FMU-VDD_3V3: C603.P$1 (1), C604.P$1 (1), C606.P$1 (1), C607.P$1 (1), C608.P$1 (1), C610.P$1 (1), C612.P$1 (1), C616.P$1 (1), D2.A, R602.P$2 (2), R604.P$2 (2), U101.11 (VDD), U101.19 (VDD), U101.21 (VREF+), U101.22 (VDDA), U101.28 (VDD), U101.50 (VDD), U101.75 (VDD), U101.100 (VDD), U603.7 (VOUT2); also elsewhere on the board
FMU-VDD_5V5: C601.P$1 (1), C615.P$1 (1), L603.P$2, R603.P$1 (1), U603.1 (VIN), U603.4 (EN2)
GND: B601.2 (NEG), C601.P$2 (2), C602.P$1 (1), C603.P$2 (2), C604.P$2 (2), C605.P$2 (2), C606.P$2 (2), C607.P$2 (2), C608.P$2 (2), C609.P$1 (1), C610.P$2 (2), C611.P$2 (2), C612.P$2 (2), C613.P$2 (2), C614.P$2 (2), C615.P$2 (2), C616.P$2 (2), C617.P$2 (2), C618.P$2 (2), L603.P$3, L603.P$4, L603.P$5, R610.P$2 (2), R611.P$1 (1), R615.P$2 (2), R616.P$2 (2), R617.P$2 (2), R621.1, S601.B3 (2), U101.10 (VSS), U101.20 (VSSA), U101.27 (VSS), U101.74 (VSS), U101.99 (VSS), U601.2 (VSS), U601.6 (VBAT), U601.GND (VSS), U601.P$2 (VSS), U601.P$3 (VSS), U602.2 (VSS), U602.6 (VBAT), U602.GND (VSS), U602.P$2 (VSS), U602.P$3 (VSS), U603.2 (GND), U603.GND; also elsewhere on the board
unnamed: C613.P$1 (1), U101.73 (VCAP_2)
unnamed: C602.P$2 (2), U603.6 (CSET)
unnamed: C611.P$1 (1), U101.49 (VCAP_1)
unnamed: D2.C, R608.P$2 (2)
unnamed: R616.P$1 (1), U602.7 (ILIM)
unnamed: Q601.C, R621.2
unnamed: Q601.B, R620.P$1 (1)
unnamed: R617.P$1 (1), U601.7 (ILIM)
VBAT: B601.1 (POS), R608.P$1 (1), U101.6 (VBAT); also elsewhere on the board
VDD_3V3_SENSORS: C605.P$1 (1), C617.P$1 (1), Q601.E, U603.8 (VOUT1); also elsewhere on the board
VDD_3V3_SENSORS_EN: R603.P$2 (2), R620.P$2 (2), R635.P$2 (2), U603.5 (EN1); also elsewhere on the board
VDD_5V_HIPOWER: C614.P$1 (1), U601.8 (OUT); also elsewhere on the board
VDD_5V_IN: L603.P$1, R609.P$2 (2), U601.1 (IN), U602.1 (IN); also elsewhere on the board
VDD_5V_PERIPH: C618.P$1 (1), U602.8 (OUT); also elsewhere on the board
VDD_5V_SENS: R609.P$1 (1), R610.P$1 (1); also elsewhere on the board

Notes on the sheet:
FMU Power and Reset
Bypass caps as close to device pins as possible.
Note: Maximise copper area connected to center ground pad.
POR reset delay 1s / uF
Current Limits: I(limit) = 25000 / R(ilim) 25K = 1A, 16K5 = 1.5A
Drain resistor for Sensor Power Rail
Note: Do not populate R603 and R635. Only one may be populated at a time. (R603, R635 is DNP)

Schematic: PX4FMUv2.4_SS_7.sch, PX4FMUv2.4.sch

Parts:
C701: 0u1; PIXHAWK2_0402-CAP
C702: 1u0; PIXHAWK2_0603-CAP
C703: 5n6; PIXHAWK2_0402-CAP
C704: 0u47; PIXHAWK2_0402-CAP
D701: PESD0402-140; PIXHAWK2_0402-TVS
J701: DF13C-2P-1.25V; CON-HIROSE-DF13_DF13C-2P-1.25V
J702: DF13C-3P-1.25V; CON-HIROSE-DF13_DF13C-3P-1.25V
L701: 47uH; PIXHAWK2_0805-IND
LED701, LED703: AMBER; PIXHAWK2_0603-LED
LED702, LED704: GREEN; PIXHAWK2_0603-LED
LED705: BLUE; PIXHAWK2_0603-LED
R3, R4, R707, R708, R709, R711, R712: 220R; PIXHAWK2_0402-RES
R701: 9K09; PIXHAWK2_0402-RES
R702, R704: 10K; PIXHAWK2_0402-RES
R703: 100K; PIXHAWK2_0402-RES
R705: 453K; PIXHAWK2_0402-RES
R706: 16K5; PIXHAWK2_0402-RES
R710: 68R; PIXHAWK2_0402-RES
R713: 1K5; PIXHAWK2_0402-RES
U701: TCA62724FMG; PIXHAWK2_SON10
U702: LT3469; PIXHAWK2_SOT23-8
U703: LRTB GFTG-T7AW-1+V7A7-29+R5T9-49-L; PIXHAWK2_6-PLCC

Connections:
!FMU-LED_AMBER: R707.P$1 (1); also elsewhere on the board
!IO-LED_AMBER: R709.P$1 (1); also elsewhere on the board
!IO-LED_BLUE: R712.P$1 (1); also elsewhere on the board
!IO-LED_SAFETY: R710.P$2 (2); also elsewhere on the board
ALARM: R701.P$2 (2); also elsewhere on the board
FMU-!RESET: U701.4 (!RESET); also elsewhere on the board
FMU-I2C2_SCL: U701.3 (SCL); also elsewhere on the board
FMU-I2C2_SDA: U701.2 (SDA); also elsewhere on the board
FMU-VDD_3V3: C701.P$1 (1), U701.1 (!SHDN), U701.10 (VIN); also elsewhere on the board
GND: C701.P$2 (2), C702.P$2 (2), C703.P$2 (2), C704.P$2 (2), D701.A, J701.2, R702.P$2 (2), R704.P$1 (1), R706.P$2 (2), R708.P$1 (1), R711.P$1 (1), R713.P$2 (2), U701.5 (GND), U702.4 (GND); also elsewhere on the board
IO-VDD_3V3: D701.C, J702.1; also elsewhere on the board
IO-VDD_5V5: LED702.A, LED703.A, LED705.A; also elsewhere on the board
unnamed: LED704.C, R711.P$2 (2)
unnamed: LED705.C, R712.P$2 (2)
unnamed: R3.P$1 (1), R707.P$2 (2)
unnamed: R705.P$2 (2), R706.P$1 (1), U702.2 (FB)
unnamed: R702.P$1 (1), R703.P$2 (2), U702.8 (-IN)
unnamed: LED701.C, R3.P$2 (2)
unnamed: C703.P$1 (1), J701.1, R703.P$1 (1), U702.1 (OUT)
unnamed: R701.P$1 (1), U702.7 (+IN)
unnamed: LED702.C, R708.P$2 (2)
unnamed: L701.P$2 (2), U702.5 (SW)
unnamed: C704.P$1 (1), R705.P$1 (1), U702.6 (VCC)
unnamed: R4.P$1 (1), R709.P$2 (2)
unnamed: LED703.C, R4.P$2 (2)
unnamed: J702.2, R710.P$1 (1)
unnamed: R704.P$2 (2), U701.6 (REXT)
RGB_LED_3: U701.9 (OUT0), U703.C1 (C)
RGB_LED_4: U701.8 (OUT1), U703.C2 (C)
RGB_LED_14: U701.7 (OUT2), U703.C3 (C)
SAFETY: J702.3, R713.P$1 (1); also elsewhere on the board
VDD_5V_IN: C702.P$1 (1), L701.P$1 (1), LED701.A, LED704.A, U702.3 (VIN), U703.A1 (A), U703.A2 (A), U703.A3 (A); also elsewhere on the board

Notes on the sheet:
LEDs Piezo driver Safety switch
Switch: E-Switch LP1OA1AR
SAFETY
LED should be Omron LRTBG6SG-U4AA-1+V2B4-25+S or similar 6PLCC high-brigtness type.
Iout = (1.17 / REXT) * 460 10K = 54mA, selected for maximum daylight visibility.
Note: LED driver is on FMU-I2C2 so that an external instance can be connected to FMU-I2C1.
All LEDs nominal target 60mcd for good daylight visibility. Resistor values have been adjusted to optimize BOM. Green: APG1608CGKC/T Vf(typ): 2.1V Target If: 20mA Selected R: 220 Cacluated If @ 5.5V: 15mA Amber: APT1608SECK Vf(typ): 2.1V Target If: 5mA Selected R: 440 Cacluated If @ 5.5V: 8mA Blue: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
Component values taken directly from the LTC evaluation design. Note that the ALARM input should idle low to minimise power dissipation.

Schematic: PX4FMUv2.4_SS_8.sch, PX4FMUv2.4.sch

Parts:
C801, C802, C803, C804: 0u1; PIXHAWK2_0402-CAP
C805, C806: 8p; PIXHAWK2_0402-CAP
D801: PESD0402-140; PIXHAWK2_0402-TVS
J801: JST-ZH-3; FOR-TRANSFERS_JST-ZH-SMT-VERTICAL
JX801: HEADER-3X1BOARDEDGE-SHORT; PIXHAWK2_HEADER_3X01_SMD_H_BOARD_EDGE_SHORT
JX802: ARM_MINI_JTAG-SMT; PIXHAWK2_FTSH-105-01-XXX-DV-K
R801, R802: 10K; PIXHAWK2_0402-RES
R803, R804: 220R; PIXHAWK2_0402-RES
S801: RESET; PIXHAWK2_EVQP7J01K
U801: STM32F10XCXT6; PIXHAWK2_TQFP48
X801: 3.2x2.5 mm / 24 MHz / 15 ppm; PIXHAWK2_OSCILLATOR-3.2X2.5

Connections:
!IO-LED_AMBER: U801.28 (PB15); also elsewhere on the board
!IO-LED_BLUE: U801.27 (PB14); also elsewhere on the board
!IO-LED_SAFETY: U801.26 (PB13); also elsewhere on the board
!SBUS_OUTPUT_EN: U801.40 (PB4); also elsewhere on the board
GND: C801.P$1 (1), C802.P$2 (2), C803.P$2 (2), C804.P$2 (2), C805.P$2 (2), C806.P$1 (1), D801.A, J801.P$2, JX801.3 (GND), JX802.3, JX802.5, JX802.9, R801.P$2 (2), R802.P$2 (2), S801.B3 (2), U801.8 (VSSA), U801.23 (VSS_1), U801.35 (VSS_2), U801.47 (VSS_3), X801.2 (NC_2), X801.4 (NC_4); also elsewhere on the board
IO-!RESET: C801.P$2 (2), S801.A1 (1), U801.7 (NRST); also elsewhere on the board
IO-!VDD_SERVO_IN_FAULT: U801.38 (PA15); also elsewhere on the board
IO-BOOT0: R801.P$1 (1), U801.44 (BOOT0); also elsewhere on the board
IO-BOOT1: R802.P$1 (1), U801.20 (PB2)
IO-CH1: U801.10 (PA0); also elsewhere on the board
IO-CH2: U801.11 (PA1); also elsewhere on the board
IO-CH3: U801.45 (PB8); also elsewhere on the board
IO-CH4: U801.46 (PB9); also elsewhere on the board
IO-CH5: U801.16 (PA6); also elsewhere on the board
IO-CH6: U801.17 (PA7); also elsewhere on the board
IO-CH7: U801.18 (PB0); also elsewhere on the board
IO-CH8: U801.19 (PB1); also elsewhere on the board
IO-SWCLK: JX802.4, U801.37 (PA14)
IO-SWDIO: JX802.2, U801.34 (PA13)
IO-SWO: JX802.6, U801.39 (PB3)
IO-USART1_RX: J801.P$3, JX801.2 (+5V), U801.31 (PA10)
IO-USART1_TX: JX801.1 (PPM), U801.30 (PA9); also elsewhere on the board
IO-VDD_3V3: C802.P$1 (1), C803.P$1 (1), C804.P$1 (1), JX802.1, U801.9 (VDDA), U801.24 (VDD_1), U801.36 (VDD_2), U801.48 (VDD_3); also elsewhere on the board
unnamed: R803.P$1 (1), U801.12 (PA2)
unnamed: R804.P$1 (1), U801.13 (PA3)
unnamed: C806.P$2 (2), U801.6 (PD1/OSC=>), X801.1
unnamed: C805.P$1 (1), U801.5 (PD0/OSC<=), X801.3
PPM_INPUT: U801.29 (PA8); also elsewhere on the board
RSSI_IN: U801.15 (PA5), U801.33 (PA12); also elsewhere on the board
SAFETY: U801.41 (PB5); also elsewhere on the board
SBUS_INPUT: U801.22 (PB11); also elsewhere on the board
SBUS_OUTPUT: U801.21 (PB10); also elsewhere on the board
SERIAL_FMU_TO_IO: R804.P$2 (2); also elsewhere on the board
SERIAL_IO_TO_FMU: R803.P$2 (2); also elsewhere on the board
VBAT: U801.1 (VBAT); also elsewhere on the board
VDD_3V3_SPEKTRUM: D801.C, J801.P$1; also elsewhere on the board
VDD_3V3_SPEKTRUM_EN: U801.2 (PC13); also elsewhere on the board
VDD_SERVO_SENS: U801.14 (PA4); also elsewhere on the board

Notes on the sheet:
IO SoC Ports Spektrum/DSM port
LED3 moves to PB13 to make room for S.Bus output
Routed to FMU for debug purposes
IO_SERIAL1
Spektrum/DSM
Timer allocation: PA0: TIM2_CH1: IO-CH1 PA1: TIM2_CH2: IO-CH2 PB8: TIM4_CH3: IO-CH3 PB9: TIM4_CH4: IO-CH4 PA6: TIM3_CH1: IO-CH5 PA7: TIM3_CH2: IO-CH6 PB0: TIM3_CH3: IO-CH7 PB1: TIM3_CH4: IO-CH8 PA8: TIM1_CH1: PPM_IN PA11: TIM1_CH4: RSSI_IN
spare pwm
spare gpio

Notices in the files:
examples/OLINUXINO/A10-A20-OLINUXINO-MICRO-4GB_Rev_D/kicad_files/A10-A20-OLINUXINO-MICRO-4GB_Rev_D.sch:
This hardware design by Olimex LTD is licensed under a Creative Commons Attribution-ShareAlike 3.0 Unported License.
examples/PIXHAWK/kicad_files/PX4FMUv2.4.kicad_pcb:
(c) 2013 mjs/lm/jo
examples/RGB_LED_1.4/kicad_files/RGB LED 1.4.kicad_pcb:
(C) 2009 Ben Combee, (CC)-BY-SA 3.0
